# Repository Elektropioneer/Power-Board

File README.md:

# Power-Board
Power board with regulators

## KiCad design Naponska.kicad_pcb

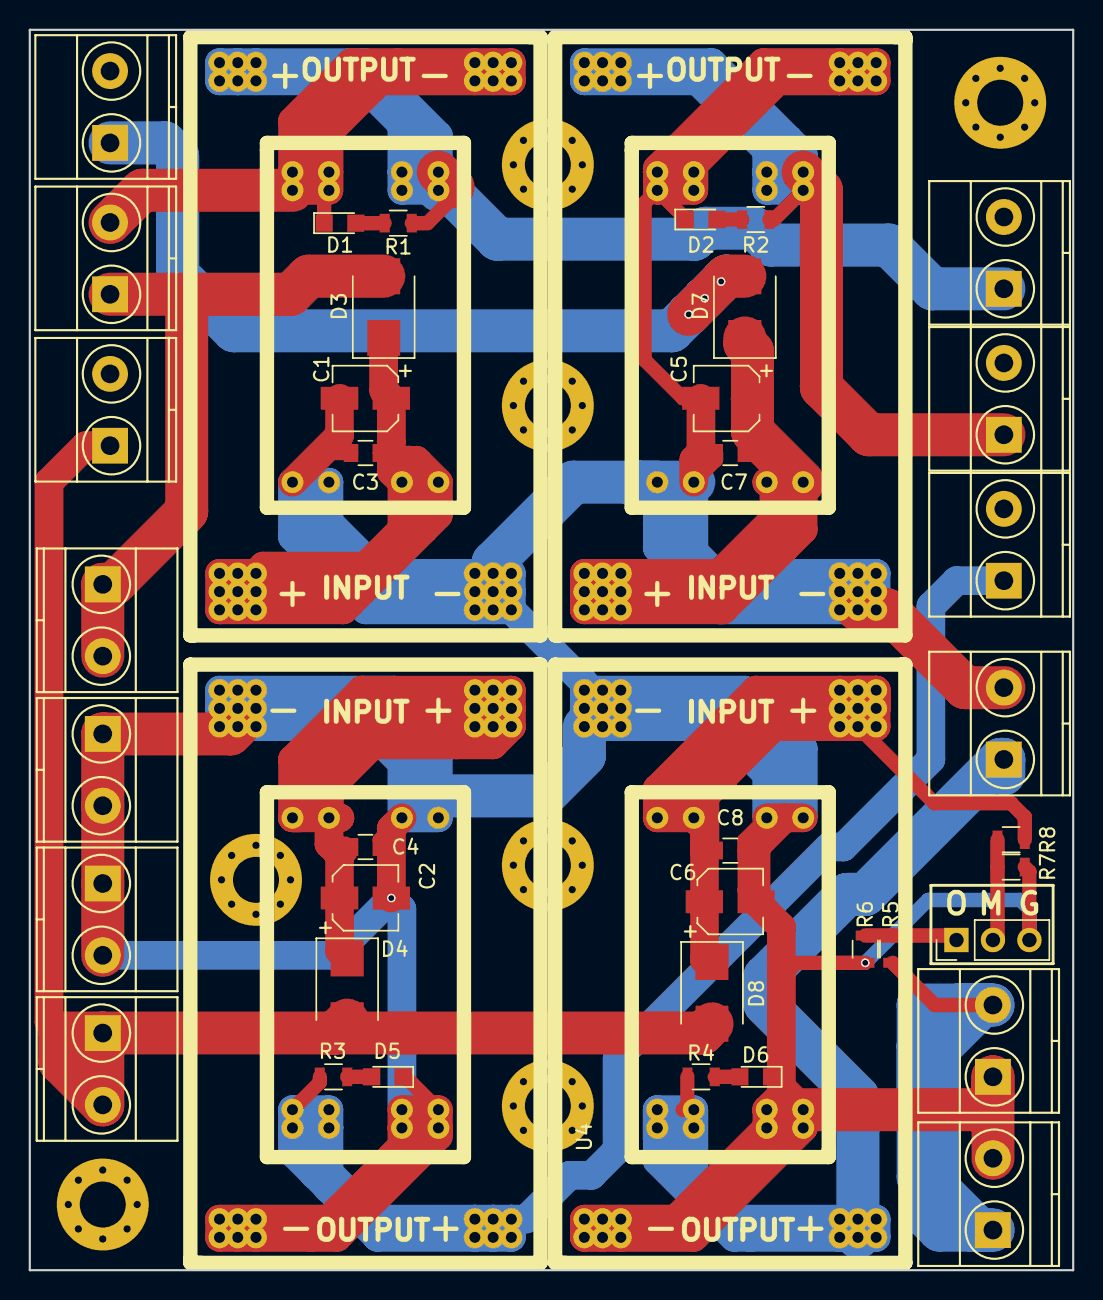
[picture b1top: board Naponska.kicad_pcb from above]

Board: 2 copper layers, 72.6 x 86.4 mm, 49 parts (0 on the bottom side), 19 nets.

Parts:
C1, C2, C5, C6: CP; CP_Elec_4x4.5
C3, C4, C7, C8: C; C_0805
D1, D2, D5, D6: LED; LED_0805
D3, D4, D7, D8: D; D_SMB_Standard
J1: INPUT_1; TerminalBlock_Pheonix_MKDS1.5-2pol
J2: INPUT_2; TerminalBlock_Pheonix_MKDS1.5-2pol
J3: INPUT_3; TerminalBlock_Pheonix_MKDS1.5-2pol
J4: INPUT_O; TerminalBlock_Pheonix_MKDS1.5-2pol
J5, J12: OUTPUT_12V_1; TerminalBlock_Pheonix_MKDS1.5-2pol
J6, J13: OUTPUT_12V_2; TerminalBlock_Pheonix_MKDS1.5-2pol
J7: OUTPUT_O; TerminalBlock_Pheonix_MKDS1.5-2pol
J8: OUTPUT_5V; TerminalBlock_Pheonix_MKDS1.5-2pol
J9: OUTPUT_SERVO; TerminalBlock_Pheonix_MKDS1.5-2pol
J10: OUTPUT_RPI; TerminalBlock_Pheonix_MKDS1.5-2pol
J11: OUTPUT_CUSTOM; TerminalBlock_Pheonix_MKDS1.5-2pol
J14: CONN_01X03; Pin_Header_Straight_1x03_Pitch2.54mm
MK2, MK3, MK4, MK5, MK6, MK7, MK8: Mounting_Hole; MountingHole_3.2mm_M3_Pad_Via
R1, R2, R3, R4, R5, R6, R7, R8: R; R_0805
U1: 5v_logic; buck
U2, U3, U4: 5v_servo; buck

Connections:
5V_LOGIC: J8.1, R1.1, U1.4
5V_RPI: J10.1, R2.1, U2.4
5V_SERVO: J9.1, R3.1, U3.4
12V_1: D3.2, J1.1, J5.1, J5.2
12V_2: D4.2, D8.2, J2.1, J12.1, J12.2
12V_3: D7.2, J3.1
12V_ODO: J4.1, J7.2, R5.1
CUSTOM: J11.1, R4.1, U4.4
GND: C1.2, C2.2, C3.2, C4.2, C5.2, C6.2, C7.2, C8.2, D1.1, D2.1, D5.1, D6.1, J1.2, J2.2, J3.2, J4.2, J6.1, J6.2, J7.1, J8.2, J9.2, J10.2, J11.2, J13.1, J13.2, J14.3, R6.2, R8.2, U1.1, U1.3, U2.1, U2.3, U3.1, U3.3, U4.1, U4.3
IN_5V_LOGIC: C1.1, C3.1, D3.1, U1.2
IN_5V_RPI: C5.1, C7.1, D7.1, U2.2
IN_5V_SERVO: C2.1, C4.1, D4.1, U3.2
IN_CUSTOM: C6.1, C8.1, D8.1, R7.1, U4.2
unnamed: D1.2, R1.2
unnamed: D2.2, R2.2
unnamed: D5.2, R3.2
unnamed: D6.2, R4.2
unnamed: J14.1, R5.2, R6.1
unnamed: J14.2, R7.2, R8.1

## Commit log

2018-02-14 Main files
2018-02-26 Added gerber
